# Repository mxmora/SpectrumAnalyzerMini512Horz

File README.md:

# SpectrumAnalyzerMini512Horz
SpectrumAnalyzerMini512Horz

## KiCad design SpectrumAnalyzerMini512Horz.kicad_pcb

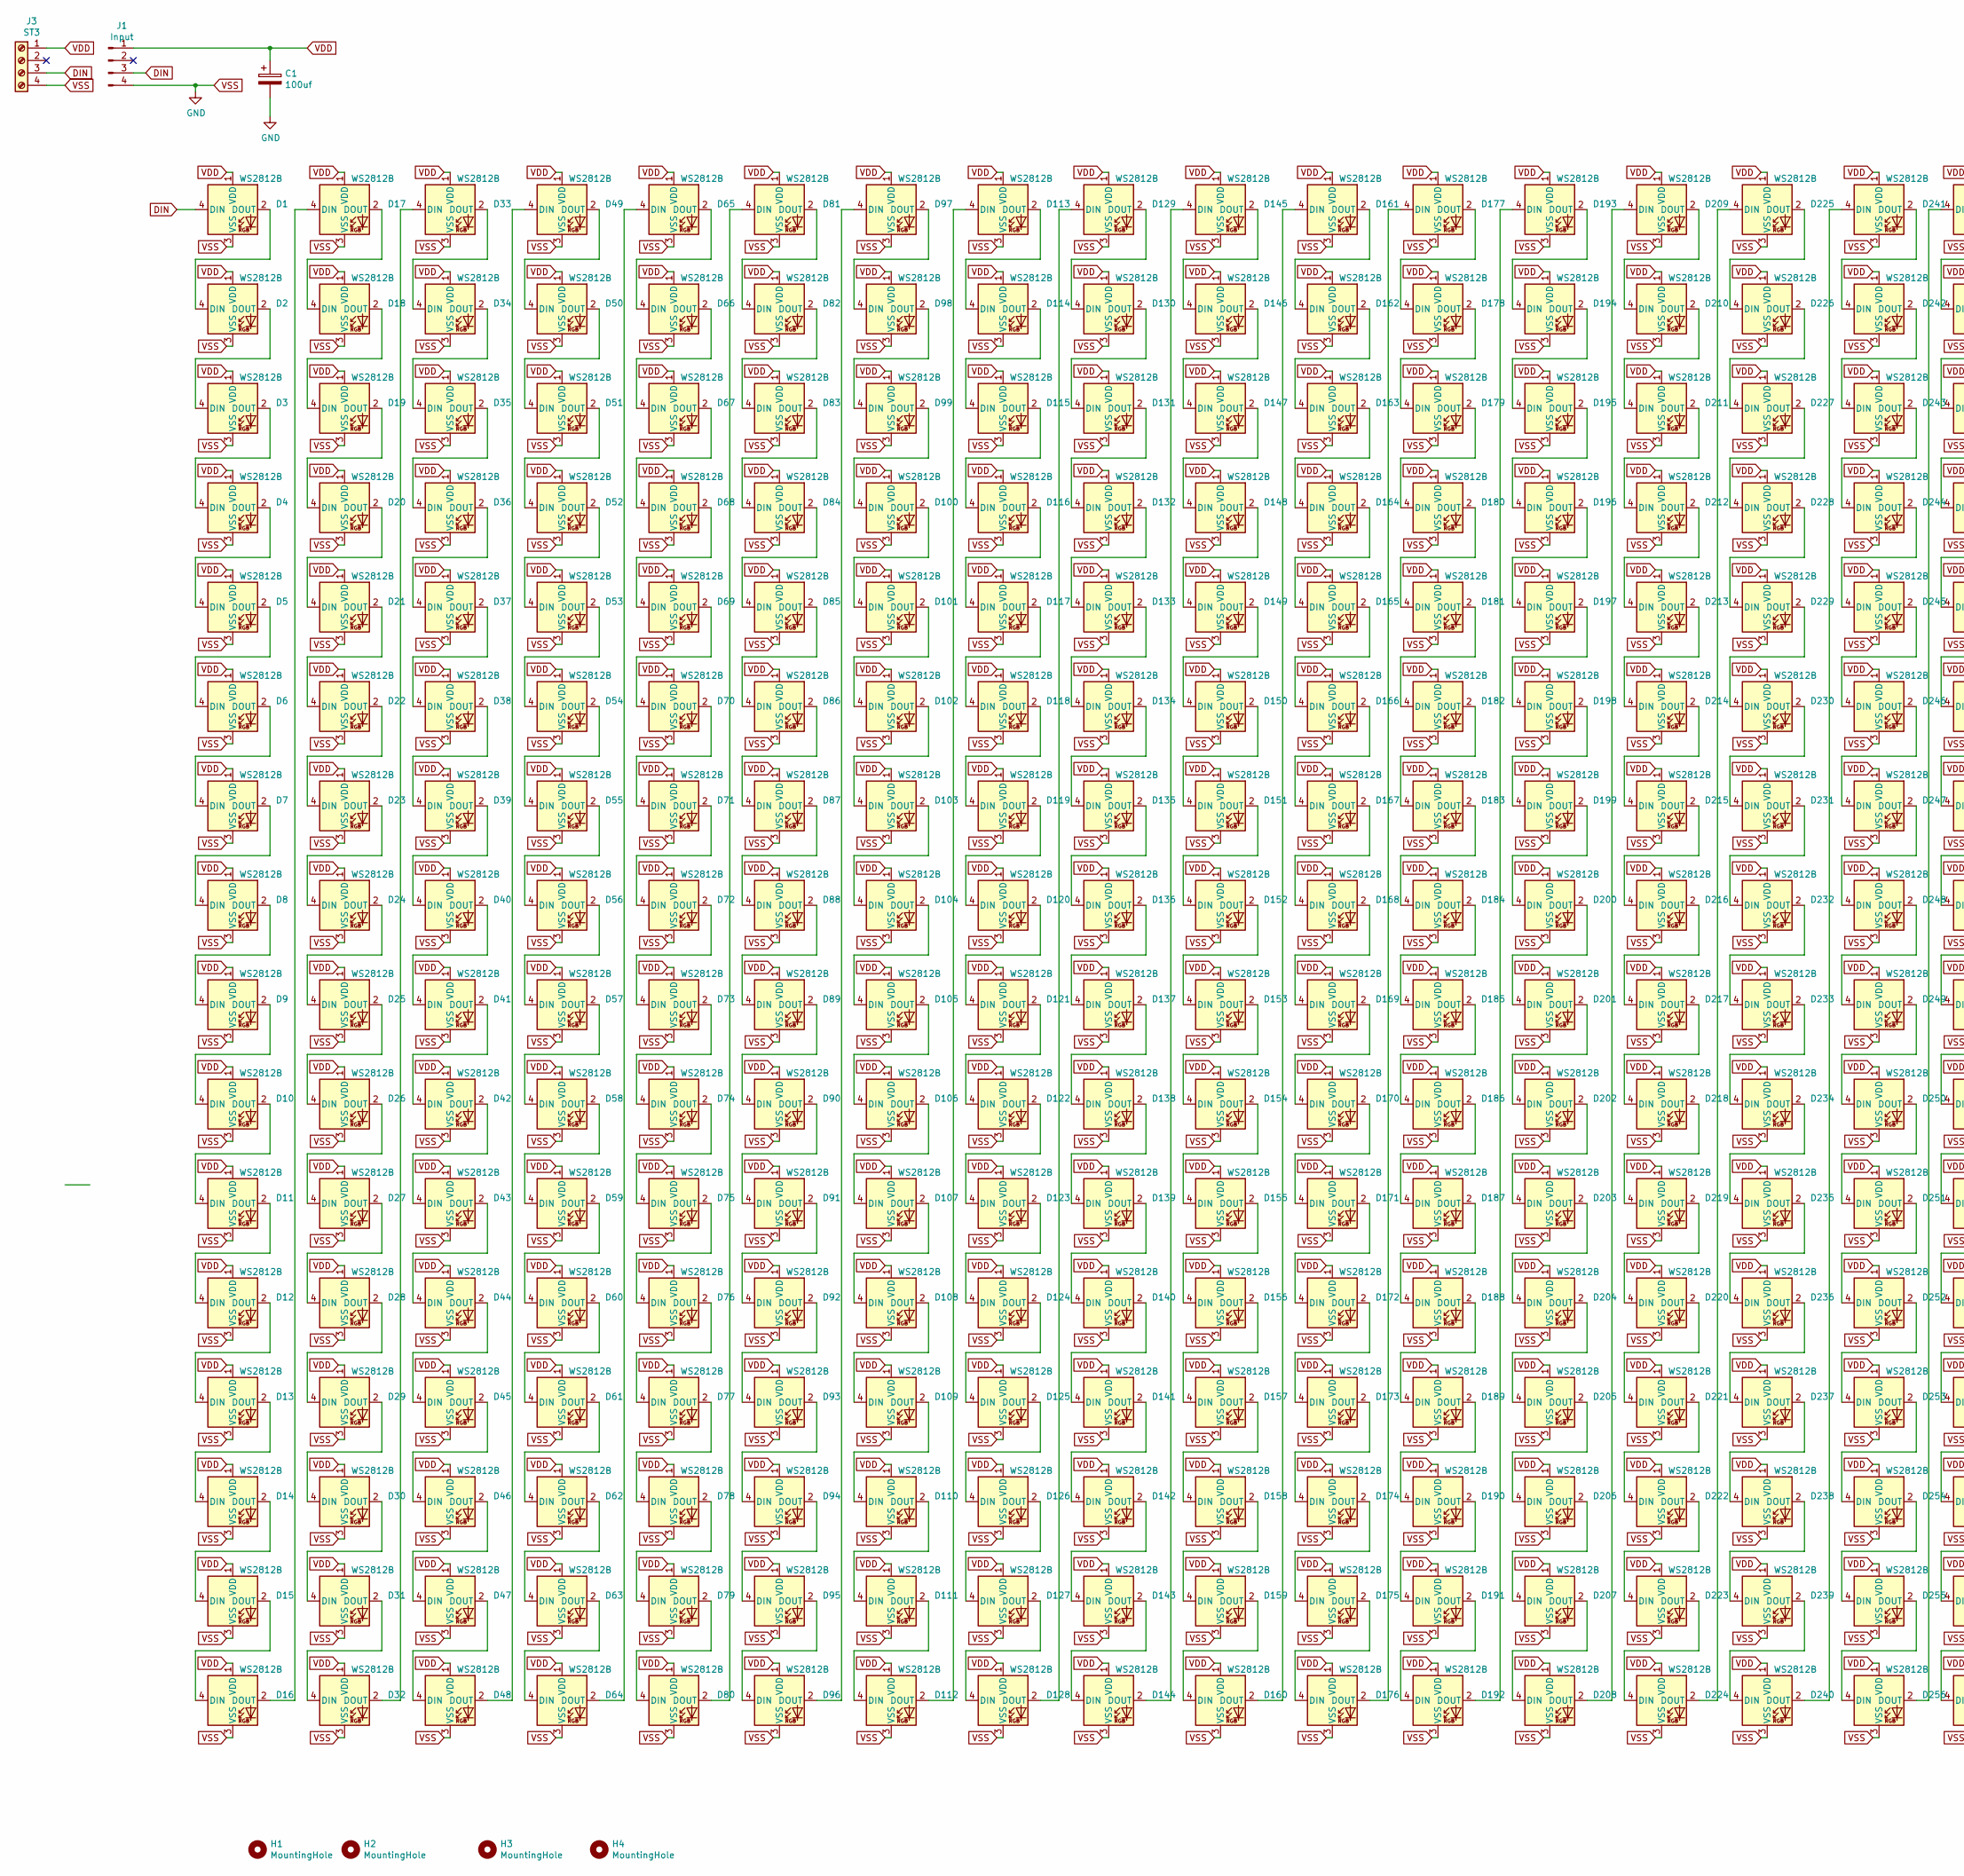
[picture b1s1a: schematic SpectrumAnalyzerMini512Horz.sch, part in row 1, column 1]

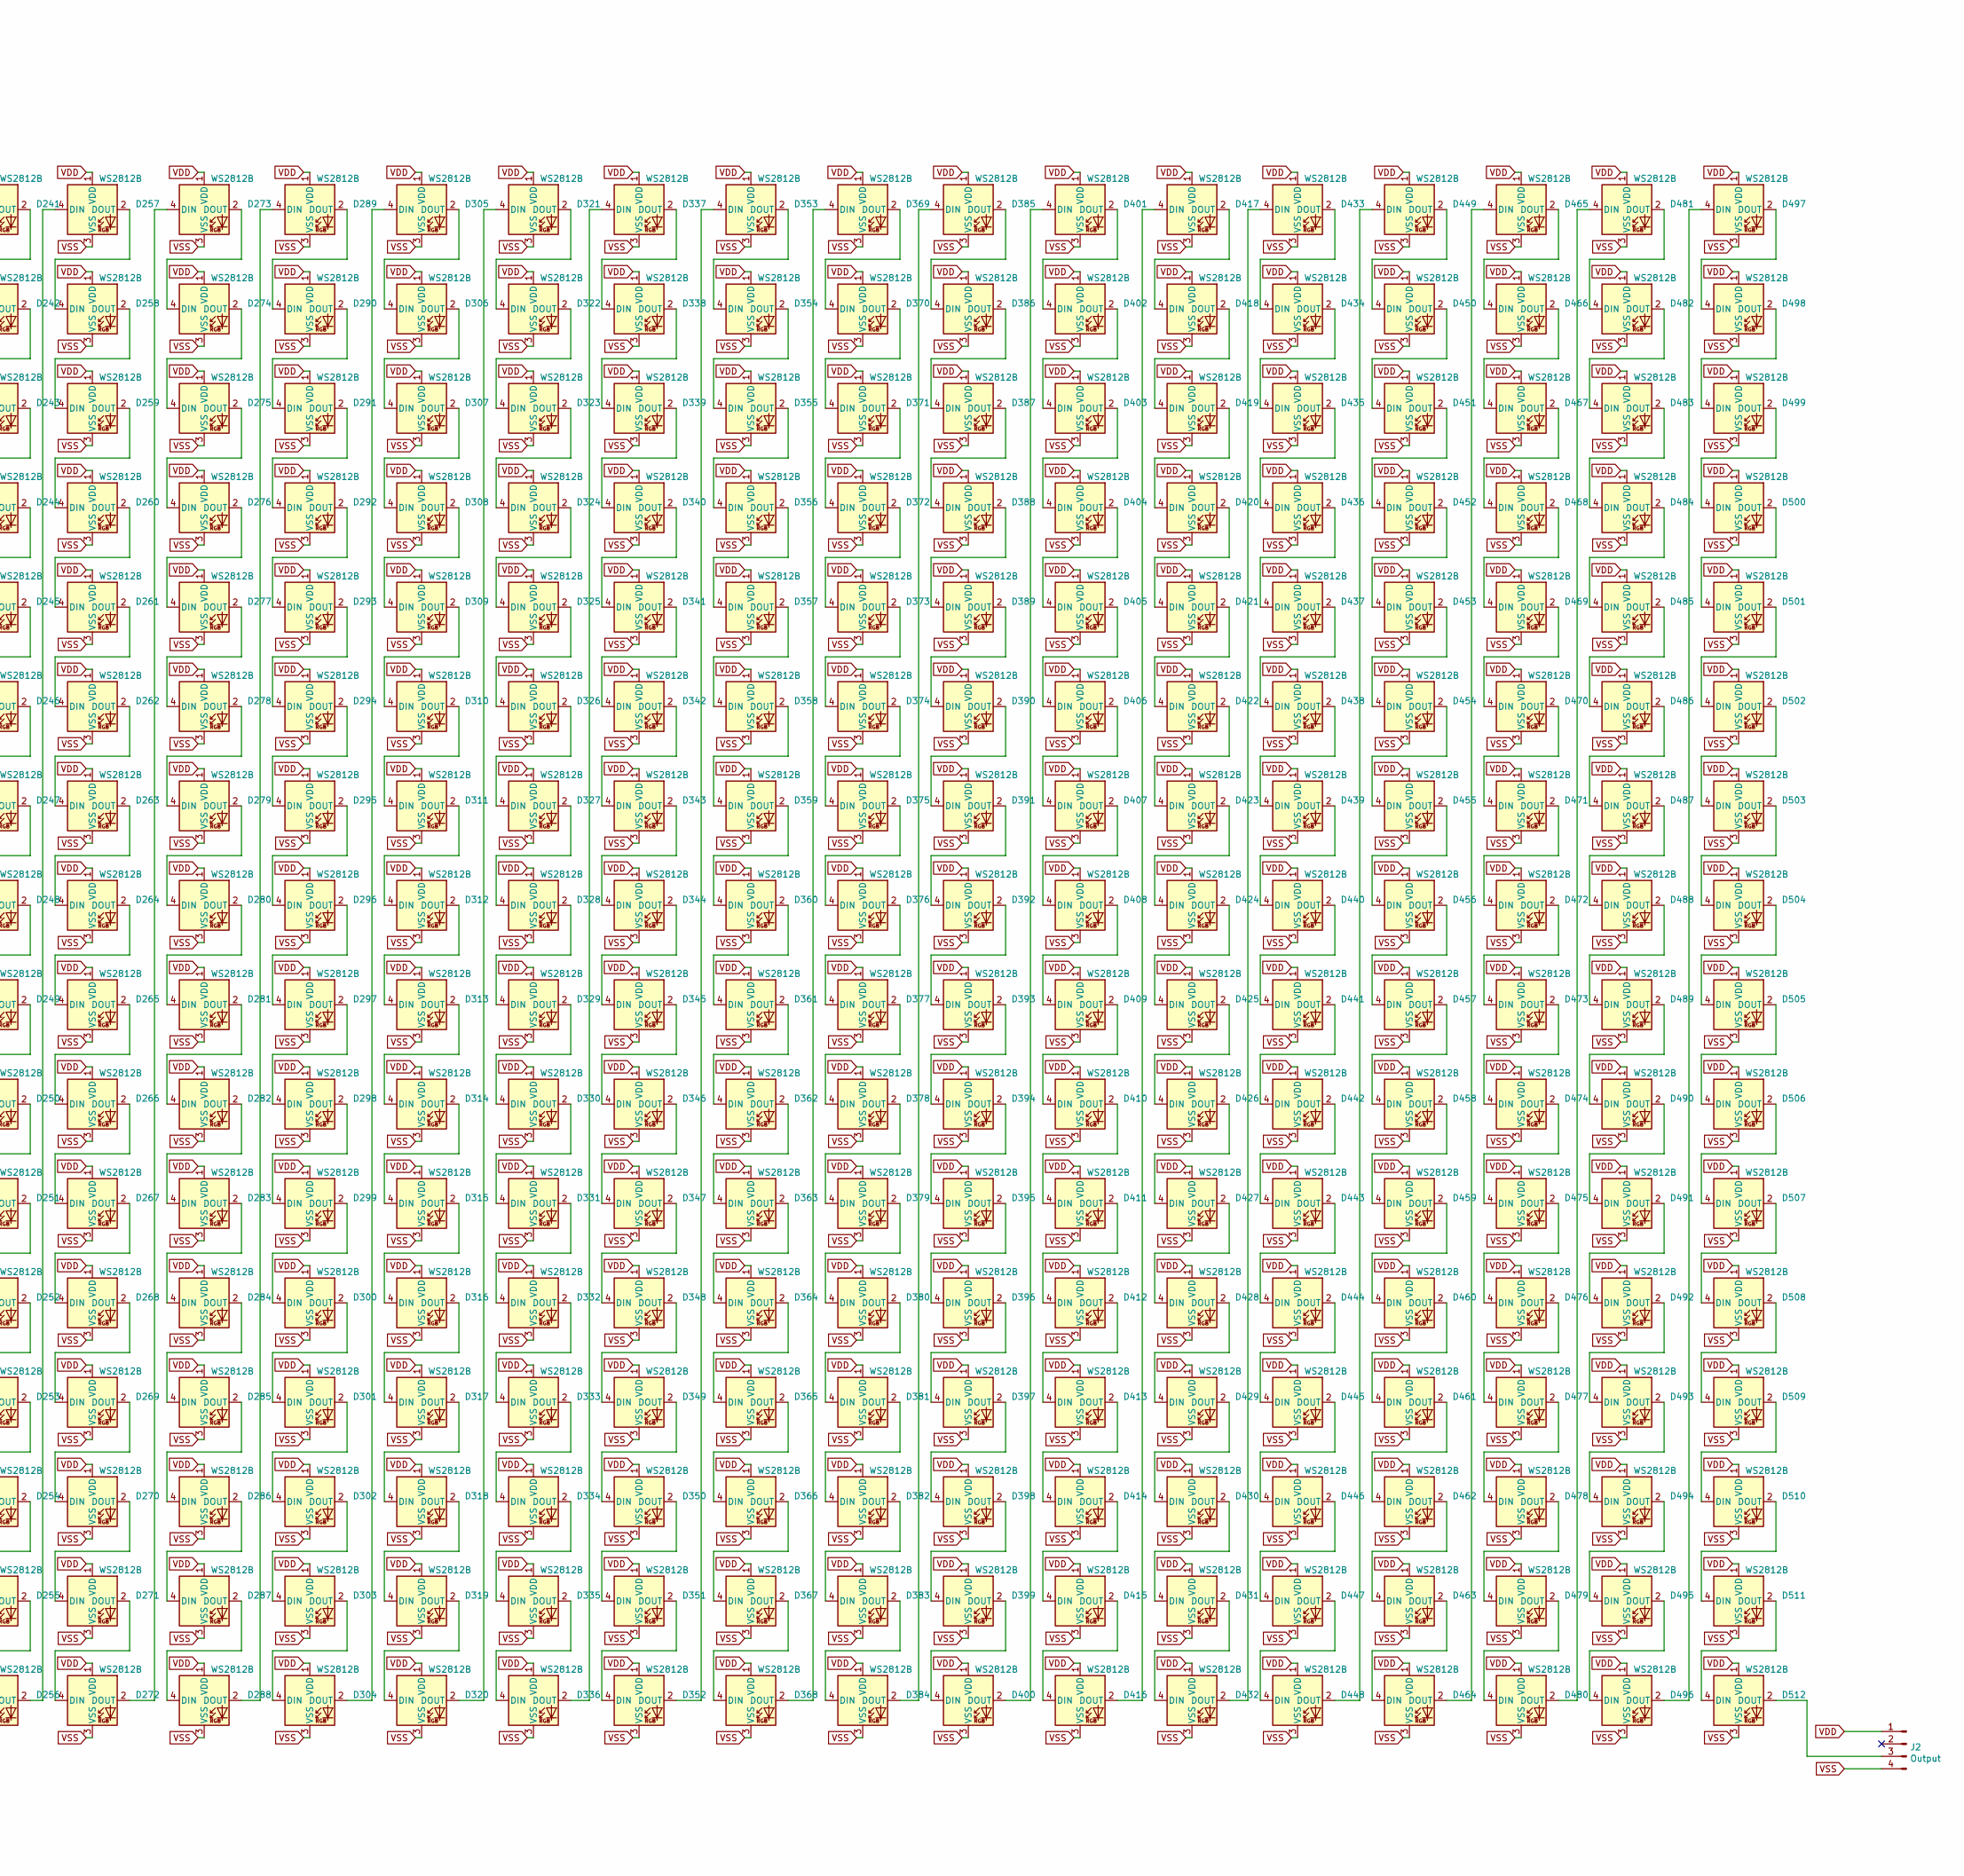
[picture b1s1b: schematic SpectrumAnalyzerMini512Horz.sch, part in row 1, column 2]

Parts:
C1: 100uf; CP_Radial_D5.0mm_P2.50mm
D1, D257: WS2812B; LED_SK6812MINI_PLCC4_3.5x3.5mm_P1.75mm; LCSC C114586
D2, D3, D4, D5, D6, D7, D8, D9, D10, D11, D12, D13, D14, D15, D16, D17, D18, D19, D20, D21, D22, D23, D24, D25, D26, D27, D28, D29, D30, D31, D32, D33, D34, D35, D36, D37, D38, D39, D40, D41, D42, D43, D44, D45, D46, D47, D48, D49, D50, D51, D52, D53, D54, D55, D56, D57, D58, D59, D60, D61, D62, D63, D64, D65, D66, D67, D68, D69, D70, D71, D72, D73, D74, D75, D76, D77, D78, D79, D80, D81, D82, D83, D84, D85, D86, D87, D88, D89, D90, D91, D92, D93, D94, D95, D96, D97, D98, D99, D100, D101, D102, D103, D104, D105, D106, D107, D108, D109, D110, D111, D112, D113, D114, D115, D116, D117, D118, D119, D120, D121, D122, D123, D124, D125, D126, D127, D128, D129, D130, D131, D132, D133, D134, D135, D136, D137, D138, D139, D140, D141, D142, D143, D144, D145, D146, D147, D148, D149, D150, D151, D152, D153, D154, D155, D156, D157, D158, D159, D160, D161, D162, D163, D164, D165, D166, D167, D168, D169, D170, D171, D172, D173, D174, D175, D176, D177, D178, D179, D180, D181, D182, D183, D184, D185, D186, D187, D188, D189, D190, D191, D192, D193, D194, D195, D196, D197, D198, D199, D200, D201, D202, D203, D204, D205, D206, D207, D208, D209, D210, D211, D212, D213, D214, D215, D216, D217, D218, D219, D220, D221, D222, D223, D224, D225, D226, D227, D228, D229, D230, D231, D232, D233, D234, D235, D236, D237, D238, D239, D240, D241, D242, D243, D244, D245, D246, D247, D248, D249, D250, D251, D252, D253, D254, D255, D256, D258, D259, D260, D261, D262, D263, D264, D265, D266, D267, D268, D269, D270, D271, D272, D273, D274, D275, D276, D277, D278, D279, D280, D281, D282, D283, D284, D285, D286, D287, D288, D289, D290, D291, D292, D293, D294, D295, D296, D297, D298, D299, D300, D301, D302, D303, D304, D305, D306, D307, D308, D309, D310, D311, D312, D313, D314, D315, D316, D317, D318, D319, D320, D321, D322, D323, D324, D325, D326, D327, D328, D329, D330, D331, D332, D333, D334, D335, D336, D337, D338, D339, D340, D341, D342, D343, D344, D345, D346, D347, D348, D349, D350, D351, D352, D353, D354, D355, D356, D357, D358, D359, D360, D361, D362, D363, D364, D365, D366, D367, D368, D369, D370, D371, D372, D373, D374, D375, D376, D377, D378, D379, D380, D381, D382, D383, D384, D385, D386, D387, D388, D389, D390, D391, D392, D393, D394, D395, D396, D397, D398, D399, D400, D401, D402, D403, D404, D405, D406, D407, D408, D409, D410, D411, D412, D413, D414, D415, D416, D417, D418, D419, D420, D421, D422, D423, D424, D425, D426, D427, D428, D429, D430, D431, D432, D433, D434, D435, D436, D437, D438, D439, D440, D441, D442, D443, D444, D445, D446, D447, D448, D449, D450, D451, D452, D453, D454, D455, D456, D457, D458, D459, D460, D461, D462, D463, D464, D465, D466, D467, D468, D469, D470, D471, D472, D473, D474, D475, D476, D477, D478, D479, D480, D481, D482, D483, D484, D485, D486, D487, D488, D489, D490, D491, D492, D493, D494, D495, D496, D497, D498, D499, D500, D501, D502, D503, D504, D505, D506, D507, D508, D509, D510, D511, D512: WS2812B; LED_SK6812MINI_PLCC4_3.5x3.5mm_P1.75mm
H1, H2, H3, H4: MountingHole; MountingHole_2.5mm
J1: Input; PinHeader_1x04_P2.54mm_Vertical
J2: Output; PinHeader_1x04_P2.54mm_Vertical
J3: ST3; TerminalBlock_Phoenix_MPT-0,5-4-2.54_1x04_P2.54mm_Horizontal

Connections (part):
DIN: D1.4 (DIN), J1.3, J3.3
unnamed: D1.2 (DOUT), D2.4 (DIN)
unnamed: D2.2 (DOUT), D3.4 (DIN)
unnamed: D3.2 (DOUT), D4.4 (DIN)
unnamed: D4.2 (DOUT), D5.4 (DIN)
unnamed: D5.2 (DOUT), D6.4 (DIN)
unnamed: D6.2 (DOUT), D7.4 (DIN)
unnamed: D7.2 (DOUT), D8.4 (DIN)
unnamed: D8.2 (DOUT), D9.4 (DIN)
unnamed: D10.2 (DOUT), D11.4 (DIN)
unnamed: D9.2 (DOUT), D10.4 (DIN)
unnamed: D11.2 (DOUT), D12.4 (DIN)
unnamed: D12.2 (DOUT), D13.4 (DIN)
unnamed: D13.2 (DOUT), D14.4 (DIN)
unnamed: D14.2 (DOUT), D15.4 (DIN)
unnamed: D15.2 (DOUT), D16.4 (DIN)
unnamed: D16.2 (DOUT), D17.4 (DIN)
unnamed: D17.2 (DOUT), D18.4 (DIN)
unnamed: D18.2 (DOUT), D19.4 (DIN)
unnamed: D19.2 (DOUT), D20.4 (DIN)
unnamed: D20.2 (DOUT), D21.4 (DIN)
unnamed: D21.2 (DOUT), D22.4 (DIN)
unnamed: D22.2 (DOUT), D23.4 (DIN)
unnamed: D23.2 (DOUT), D24.4 (DIN)
unnamed: D24.2 (DOUT), D25.4 (DIN)
unnamed: D25.2 (DOUT), D26.4 (DIN)
unnamed: D26.2 (DOUT), D27.4 (DIN)
unnamed: D27.2 (DOUT), D28.4 (DIN)
unnamed: D28.2 (DOUT), D29.4 (DIN)
unnamed: D29.2 (DOUT), D30.4 (DIN)
unnamed: D30.2 (DOUT), D31.4 (DIN)
unnamed: D31.2 (DOUT), D32.4 (DIN)
unnamed: D32.2 (DOUT), D33.4 (DIN)
unnamed: D33.2 (DOUT), D34.4 (DIN)
unnamed: D34.2 (DOUT), D35.4 (DIN)
unnamed: D35.2 (DOUT), D36.4 (DIN)
unnamed: D36.2 (DOUT), D37.4 (DIN)
unnamed: D37.2 (DOUT), D38.4 (DIN)
unnamed: D38.2 (DOUT), D39.4 (DIN)
unnamed: D39.2 (DOUT), D40.4 (DIN)
unnamed: D40.2 (DOUT), D41.4 (DIN)
unnamed: D41.2 (DOUT), D42.4 (DIN)
unnamed: D42.2 (DOUT), D43.4 (DIN)
unnamed: D43.2 (DOUT), D44.4 (DIN)
unnamed: D44.2 (DOUT), D45.4 (DIN)
unnamed: D45.2 (DOUT), D46.4 (DIN)
unnamed: D46.2 (DOUT), D47.4 (DIN)
unnamed: D47.2 (DOUT), D48.4 (DIN)
unnamed: D48.2 (DOUT), D49.4 (DIN)
unnamed: D49.2 (DOUT), D50.4 (DIN)
unnamed: D50.2 (DOUT), D51.4 (DIN)
unnamed: D51.2 (DOUT), D52.4 (DIN)
unnamed: D52.2 (DOUT), D53.4 (DIN)
unnamed: D53.2 (DOUT), D54.4 (DIN)
unnamed: D54.2 (DOUT), D55.4 (DIN)
unnamed: D55.2 (DOUT), D56.4 (DIN)
unnamed: D56.2 (DOUT), D57.4 (DIN)
unnamed: D57.2 (DOUT), D58.4 (DIN)
unnamed: D58.2 (DOUT), D59.4 (DIN)
unnamed: D59.2 (DOUT), D60.4 (DIN)
unnamed: D60.2 (DOUT), D61.4 (DIN)
unnamed: D61.2 (DOUT), D62.4 (DIN)
unnamed: D62.2 (DOUT), D63.4 (DIN)
unnamed: D63.2 (DOUT), D64.4 (DIN)
unnamed: D64.2 (DOUT), D65.4 (DIN)
unnamed: D65.2 (DOUT), D66.4 (DIN)
unnamed: D66.2 (DOUT), D67.4 (DIN)
unnamed: D67.2 (DOUT), D68.4 (DIN)
unnamed: D68.2 (DOUT), D69.4 (DIN)
unnamed: D69.2 (DOUT), D70.4 (DIN)
unnamed: D70.2 (DOUT), D71.4 (DIN)
unnamed: D71.2 (DOUT), D72.4 (DIN)
unnamed: D72.2 (DOUT), D73.4 (DIN)
unnamed: D73.2 (DOUT), D74.4 (DIN)
unnamed: D74.2 (DOUT), D75.4 (DIN)
unnamed: D75.2 (DOUT), D76.4 (DIN)
unnamed: D76.2 (DOUT), D77.4 (DIN)
unnamed: D77.2 (DOUT), D78.4 (DIN)
unnamed: D78.2 (DOUT), D79.4 (DIN)
unnamed: D79.2 (DOUT), D80.4 (DIN)
unnamed: D80.2 (DOUT), D81.4 (DIN)
unnamed: D81.2 (DOUT), D82.4 (DIN)
unnamed: D82.2 (DOUT), D83.4 (DIN)
unnamed: D83.2 (DOUT), D84.4 (DIN)
unnamed: D84.2 (DOUT), D85.4 (DIN)
unnamed: D85.2 (DOUT), D86.4 (DIN)
unnamed: D86.2 (DOUT), D87.4 (DIN)
unnamed: D87.2 (DOUT), D88.4 (DIN)
unnamed: D88.2 (DOUT), D89.4 (DIN)
unnamed: D89.2 (DOUT), D90.4 (DIN)
unnamed: D90.2 (DOUT), D91.4 (DIN)
unnamed: D91.2 (DOUT), D92.4 (DIN)
unnamed: D92.2 (DOUT), D93.4 (DIN)
unnamed: D93.2 (DOUT), D94.4 (DIN)
unnamed: D94.2 (DOUT), D95.4 (DIN)
unnamed: D95.2 (DOUT), D96.4 (DIN)
unnamed: D96.2 (DOUT), D97.4 (DIN)
unnamed: D97.2 (DOUT), D98.4 (DIN)
unnamed: D98.2 (DOUT), D99.4 (DIN)
unnamed: D100.2 (DOUT), D101.4 (DIN)
unnamed: D99.2 (DOUT), D100.4 (DIN)
unnamed: D101.2 (DOUT), D102.4 (DIN)
unnamed: D102.2 (DOUT), D103.4 (DIN)
unnamed: D103.2 (DOUT), D104.4 (DIN)
unnamed: D104.2 (DOUT), D105.4 (DIN)
unnamed: D105.2 (DOUT), D106.4 (DIN)
unnamed: D106.2 (DOUT), D107.4 (DIN)
unnamed: D107.2 (DOUT), D108.4 (DIN)
unnamed: D108.2 (DOUT), D109.4 (DIN)
unnamed: D109.2 (DOUT), D110.4 (DIN)
unnamed: D110.2 (DOUT), D111.4 (DIN)
unnamed: D111.2 (DOUT), D112.4 (DIN)
unnamed: D112.2 (DOUT), D113.4 (DIN)
unnamed: D113.2 (DOUT), D114.4 (DIN)
unnamed: D114.2 (DOUT), D115.4 (DIN)
unnamed: D115.2 (DOUT), D116.4 (DIN)
unnamed: D116.2 (DOUT), D117.4 (DIN)
unnamed: D117.2 (DOUT), D118.4 (DIN)
unnamed: D118.2 (DOUT), D119.4 (DIN)
unnamed: D119.2 (DOUT), D120.4 (DIN)
unnamed: D120.2 (DOUT), D121.4 (DIN)
unnamed: D121.2 (DOUT), D122.4 (DIN)
unnamed: D122.2 (DOUT), D123.4 (DIN)
unnamed: D123.2 (DOUT), D124.4 (DIN)
unnamed: D124.2 (DOUT), D125.4 (DIN)
unnamed: D125.2 (DOUT), D126.4 (DIN)
unnamed: D126.2 (DOUT), D127.4 (DIN)
unnamed: D127.2 (DOUT), D128.4 (DIN)
unnamed: D128.2 (DOUT), D129.4 (DIN)
unnamed: D129.2 (DOUT), D130.4 (DIN)
unnamed: D130.2 (DOUT), D131.4 (DIN)
unnamed: D131.2 (DOUT), D132.4 (DIN)
unnamed: D132.2 (DOUT), D133.4 (DIN)
unnamed: D133.2 (DOUT), D134.4 (DIN)
unnamed: D134.2 (DOUT), D135.4 (DIN)
unnamed: D135.2 (DOUT), D136.4 (DIN)
unnamed: D136.2 (DOUT), D137.4 (DIN)
unnamed: D137.2 (DOUT), D138.4 (DIN)
unnamed: D138.2 (DOUT), D139.4 (DIN)
unnamed: D139.2 (DOUT), D140.4 (DIN)
unnamed: D140.2 (DOUT), D141.4 (DIN)
unnamed: D141.2 (DOUT), D142.4 (DIN)
unnamed: D142.2 (DOUT), D143.4 (DIN)
unnamed: D143.2 (DOUT), D144.4 (DIN)
unnamed: D144.2 (DOUT), D145.4 (DIN)
unnamed: D145.2 (DOUT), D146.4 (DIN)
unnamed: D146.2 (DOUT), D147.4 (DIN)
unnamed: D147.2 (DOUT), D148.4 (DIN)
unnamed: D148.2 (DOUT), D149.4 (DIN)
unnamed: D149.2 (DOUT), D150.4 (DIN)
unnamed: D150.2 (DOUT), D151.4 (DIN)
unnamed: D151.2 (DOUT), D152.4 (DIN)
unnamed: D152.2 (DOUT), D153.4 (DIN)
unnamed: D153.2 (DOUT), D154.4 (DIN)
unnamed: D154.2 (DOUT), D155.4 (DIN)
unnamed: D155.2 (DOUT), D156.4 (DIN)
unnamed: D156.2 (DOUT), D157.4 (DIN)
unnamed: D157.2 (DOUT), D158.4 (DIN)
unnamed: D158.2 (DOUT), D159.4 (DIN)
unnamed: D159.2 (DOUT), D160.4 (DIN)
unnamed: D160.2 (DOUT), D161.4 (DIN)
unnamed: D161.2 (DOUT), D162.4 (DIN)
unnamed: D162.2 (DOUT), D163.4 (DIN)
unnamed: D163.2 (DOUT), D164.4 (DIN)
unnamed: D164.2 (DOUT), D165.4 (DIN)
unnamed: D165.2 (DOUT), D166.4 (DIN)
unnamed: D166.2 (DOUT), D167.4 (DIN)
unnamed: D167.2 (DOUT), D168.4 (DIN)
unnamed: D168.2 (DOUT), D169.4 (DIN)
unnamed: D169.2 (DOUT), D170.4 (DIN)
unnamed: D170.2 (DOUT), D171.4 (DIN)
unnamed: D171.2 (DOUT), D172.4 (DIN)
unnamed: D172.2 (DOUT), D173.4 (DIN)
unnamed: D173.2 (DOUT), D174.4 (DIN)
unnamed: D174.2 (DOUT), D175.4 (DIN)
unnamed: D175.2 (DOUT), D176.4 (DIN)
unnamed: D176.2 (DOUT), D177.4 (DIN)
unnamed: D177.2 (DOUT), D178.4 (DIN)
unnamed: D178.2 (DOUT), D179.4 (DIN)
unnamed: D179.2 (DOUT), D180.4 (DIN)
unnamed: D180.2 (DOUT), D181.4 (DIN)
unnamed: D181.2 (DOUT), D182.4 (DIN)
unnamed: D182.2 (DOUT), D183.4 (DIN)
unnamed: D183.2 (DOUT), D184.4 (DIN)
unnamed: D184.2 (DOUT), D185.4 (DIN)
unnamed: D185.2 (DOUT), D186.4 (DIN)
unnamed: D186.2 (DOUT), D187.4 (DIN)
unnamed: D187.2 (DOUT), D188.4 (DIN)
unnamed: D188.2 (DOUT), D189.4 (DIN)
unnamed: D189.2 (DOUT), D190.4 (DIN)
unnamed: D190.2 (DOUT), D191.4 (DIN)
unnamed: D191.2 (DOUT), D192.4 (DIN)
unnamed: D192.2 (DOUT), D193.4 (DIN)
unnamed: D193.2 (DOUT), D194.4 (DIN)
unnamed: D194.2 (DOUT), D195.4 (DIN)
unnamed: D195.2 (DOUT), D196.4 (DIN)
unnamed: D196.2 (DOUT), D197.4 (DIN)
unnamed: D197.2 (DOUT), D198.4 (DIN)
unnamed: D198.2 (DOUT), D199.4 (DIN)
unnamed: D199.2 (DOUT), D200.4 (DIN)
unnamed: D200.2 (DOUT), D201.4 (DIN)
unnamed: D201.2 (DOUT), D202.4 (DIN)
unnamed: D202.2 (DOUT), D203.4 (DIN)
unnamed: D203.2 (DOUT), D204.4 (DIN)
unnamed: D204.2 (DOUT), D205.4 (DIN)
unnamed: D205.2 (DOUT), D206.4 (DIN)
unnamed: D206.2 (DOUT), D207.4 (DIN)
unnamed: D207.2 (DOUT), D208.4 (DIN)
unnamed: D208.2 (DOUT), D209.4 (DIN)
unnamed: D209.2 (DOUT), D210.4 (DIN)
unnamed: D210.2 (DOUT), D211.4 (DIN)
unnamed: D211.2 (DOUT), D212.4 (DIN)
unnamed: D212.2 (DOUT), D213.4 (DIN)
unnamed: D213.2 (DOUT), D214.4 (DIN)
unnamed: D214.2 (DOUT), D215.4 (DIN)
unnamed: D215.2 (DOUT), D216.4 (DIN)
unnamed: D216.2 (DOUT), D217.4 (DIN)
unnamed: D217.2 (DOUT), D218.4 (DIN)
unnamed: D218.2 (DOUT), D219.4 (DIN)
unnamed: D219.2 (DOUT), D220.4 (DIN)
unnamed: D220.2 (DOUT), D221.4 (DIN)
unnamed: D221.2 (DOUT), D222.4 (DIN)
unnamed: D222.2 (DOUT), D223.4 (DIN)
unnamed: D223.2 (DOUT), D224.4 (DIN)
unnamed: D224.2 (DOUT), D225.4 (DIN)
unnamed: D225.2 (DOUT), D226.4 (DIN)
unnamed: D226.2 (DOUT), D227.4 (DIN)
unnamed: D227.2 (DOUT), D228.4 (DIN)
unnamed: D228.2 (DOUT), D229.4 (DIN)
unnamed: D229.2 (DOUT), D230.4 (DIN)
unnamed: D230.2 (DOUT), D231.4 (DIN)
unnamed: D231.2 (DOUT), D232.4 (DIN)
unnamed: D232.2 (DOUT), D233.4 (DIN)
unnamed: D233.2 (DOUT), D234.4 (DIN)
unnamed: D234.2 (DOUT), D235.4 (DIN)
unnamed: D235.2 (DOUT), D236.4 (DIN)
unnamed: D236.2 (DOUT), D237.4 (DIN)
unnamed: D237.2 (DOUT), D238.4 (DIN)
unnamed: D238.2 (DOUT), D239.4 (DIN)
unnamed: D239.2 (DOUT), D240.4 (DIN)
unnamed: D240.2 (DOUT), D241.4 (DIN)
unnamed: D241.2 (DOUT), D242.4 (DIN)
unnamed: D242.2 (DOUT), D243.4 (DIN)
unnamed: D243.2 (DOUT), D244.4 (DIN)
unnamed: D244.2 (DOUT), D245.4 (DIN)
unnamed: D245.2 (DOUT), D246.4 (DIN)
unnamed: D246.2 (DOUT), D247.4 (DIN)
unnamed: D247.2 (DOUT), D248.4 (DIN)
unnamed: D248.2 (DOUT), D249.4 (DIN)
unnamed: D249.2 (DOUT), D250.4 (DIN)
unnamed: D250.2 (DOUT), D251.4 (DIN)
unnamed: D251.2 (DOUT), D252.4 (DIN)
unnamed: D252.2 (DOUT), D253.4 (DIN)
unnamed: D253.2 (DOUT), D254.4 (DIN)
unnamed: D254.2 (DOUT), D255.4 (DIN)
unnamed: D255.2 (DOUT), D256.4 (DIN)
unnamed: D256.2 (DOUT), D257.4 (DIN)
unnamed: D257.2 (DOUT), D258.4 (DIN)
unnamed: D258.2 (DOUT), D259.4 (DIN)
unnamed: D259.2 (DOUT), D260.4 (DIN)
unnamed: D260.2 (DOUT), D261.4 (DIN)
unnamed: D261.2 (DOUT), D262.4 (DIN)
unnamed: D262.2 (DOUT), D263.4 (DIN)
unnamed: D263.2 (DOUT), D264.4 (DIN)
unnamed: D264.2 (DOUT), D265.4 (DIN)
unnamed: D265.2 (DOUT), D266.4 (DIN)
unnamed: D266.2 (DOUT), D267.4 (DIN)
unnamed: D267.2 (DOUT), D268.4 (DIN)
unnamed: D268.2 (DOUT), D269.4 (DIN)
unnamed: D269.2 (DOUT), D270.4 (DIN)
unnamed: D270.2 (DOUT), D271.4 (DIN)
unnamed: D271.2 (DOUT), D272.4 (DIN)
unnamed: D272.2 (DOUT), D273.4 (DIN)
unnamed: D273.2 (DOUT), D274.4 (DIN)
unnamed: D274.2 (DOUT), D275.4 (DIN)
unnamed: D275.2 (DOUT), D276.4 (DIN)
unnamed: D276.2 (DOUT), D277.4 (DIN)
unnamed: D277.2 (DOUT), D278.4 (DIN)
unnamed: D278.2 (DOUT), D279.4 (DIN)
unnamed: D279.2 (DOUT), D280.4 (DIN)
unnamed: D280.2 (DOUT), D281.4 (DIN)
unnamed: D281.2 (DOUT), D282.4 (DIN)
unnamed: D282.2 (DOUT), D283.4 (DIN)
unnamed: D283.2 (DOUT), D284.4 (DIN)
unnamed: D284.2 (DOUT), D285.4 (DIN)
unnamed: D285.2 (DOUT), D286.4 (DIN)
unnamed: D286.2 (DOUT), D287.4 (DIN)
unnamed: D287.2 (DOUT), D288.4 (DIN)
unnamed: D288.2 (DOUT), D289.4 (DIN)
unnamed: D289.2 (DOUT), D290.4 (DIN)
unnamed: D290.2 (DOUT), D291.4 (DIN)
unnamed: D291.2 (DOUT), D292.4 (DIN)
unnamed: D292.2 (DOUT), D293.4 (DIN)
unnamed: D293.2 (DOUT), D294.4 (DIN)
unnamed: D294.2 (DOUT), D295.4 (DIN)
unnamed: D295.2 (DOUT), D296.4 (DIN)
unnamed: D296.2 (DOUT), D297.4 (DIN)
unnamed: D297.2 (DOUT), D298.4 (DIN)
unnamed: D298.2 (DOUT), D299.4 (DIN)
unnamed: D299.2 (DOUT), D300.4 (DIN)
unnamed: D300.2 (DOUT), D301.4 (DIN)
unnamed: D301.2 (DOUT), D302.4 (DIN)
unnamed: D302.2 (DOUT), D303.4 (DIN)
unnamed: D303.2 (DOUT), D304.4 (DIN)
unnamed: D304.2 (DOUT), D305.4 (DIN)
unnamed: D305.2 (DOUT), D306.4 (DIN)
unnamed: D306.2 (DOUT), D307.4 (DIN)
unnamed: D307.2 (DOUT), D308.4 (DIN)
unnamed: D308.2 (DOUT), D309.4 (DIN)
unnamed: D309.2 (DOUT), D310.4 (DIN)
unnamed: D310.2 (DOUT), D311.4 (DIN)
unnamed: D311.2 (DOUT), D312.4 (DIN)
unnamed: D312.2 (DOUT), D313.4 (DIN)
unnamed: D313.2 (DOUT), D314.4 (DIN)
unnamed: D314.2 (DOUT), D315.4 (DIN)
unnamed: D315.2 (DOUT), D316.4 (DIN)
unnamed: D316.2 (DOUT), D317.4 (DIN)
unnamed: D317.2 (DOUT), D318.4 (DIN)
unnamed: D318.2 (DOUT), D319.4 (DIN)
unnamed: D319.2 (DOUT), D320.4 (DIN)
unnamed: D320.2 (DOUT), D321.4 (DIN)
unnamed: D321.2 (DOUT), D322.4 (DIN)
unnamed: D322.2 (DOUT), D323.4 (DIN)
unnamed: D323.2 (DOUT), D324.4 (DIN)
unnamed: D324.2 (DOUT), D325.4 (DIN)
unnamed: D325.2 (DOUT), D326.4 (DIN)
unnamed: D326.2 (DOUT), D327.4 (DIN)
unnamed: D327.2 (DOUT), D328.4 (DIN)
unnamed: D328.2 (DOUT), D329.4 (DIN)
unnamed: D329.2 (DOUT), D330.4 (DIN)
unnamed: D330.2 (DOUT), D331.4 (DIN)
unnamed: D331.2 (DOUT), D332.4 (DIN)
unnamed: D332.2 (DOUT), D333.4 (DIN)
unnamed: D333.2 (DOUT), D334.4 (DIN)
unnamed: D334.2 (DOUT), D335.4 (DIN)
unnamed: D335.2 (DOUT), D336.4 (DIN)
unnamed: D336.2 (DOUT), D337.4 (DIN)
unnamed: D337.2 (DOUT), D338.4 (DIN)
unnamed: D338.2 (DOUT), D339.4 (DIN)
unnamed: D339.2 (DOUT), D340.4 (DIN)
unnamed: D340.2 (DOUT), D341.4 (DIN)
unnamed: D341.2 (DOUT), D342.4 (DIN)
unnamed: D342.2 (DOUT), D343.4 (DIN)
unnamed: D343.2 (DOUT), D344.4 (DIN)
unnamed: D344.2 (DOUT), D345.4 (DIN)
unnamed: D345.2 (DOUT), D346.4 (DIN)
unnamed: D346.2 (DOUT), D347.4 (DIN)
unnamed: D347.2 (DOUT), D348.4 (DIN)
unnamed: D348.2 (DOUT), D349.4 (DIN)
unnamed: D349.2 (DOUT), D350.4 (DIN)
unnamed: D350.2 (DOUT), D351.4 (DIN)
unnamed: D351.2 (DOUT), D352.4 (DIN)
unnamed: D352.2 (DOUT), D353.4 (DIN)
unnamed: D353.2 (DOUT), D354.4 (DIN)
unnamed: D354.2 (DOUT), D355.4 (DIN)
unnamed: D355.2 (DOUT), D356.4 (DIN)
unnamed: D356.2 (DOUT), D357.4 (DIN)
unnamed: D357.2 (DOUT), D358.4 (DIN)
unnamed: D358.2 (DOUT), D359.4 (DIN)
unnamed: D359.2 (DOUT), D360.4 (DIN)
unnamed: D360.2 (DOUT), D361.4 (DIN)
unnamed: D361.2 (DOUT), D362.4 (DIN)
unnamed: D362.2 (DOUT), D363.4 (DIN)
unnamed: D363.2 (DOUT), D364.4 (DIN)
unnamed: D364.2 (DOUT), D365.4 (DIN)
unnamed: D365.2 (DOUT), D366.4 (DIN)
unnamed: D366.2 (DOUT), D367.4 (DIN)
unnamed: D367.2 (DOUT), D368.4 (DIN)
unnamed: D368.2 (DOUT), D369.4 (DIN)
unnamed: D369.2 (DOUT), D370.4 (DIN)
unnamed: D370.2 (DOUT), D371.4 (DIN)
unnamed: D371.2 (DOUT), D372.4 (DIN)
unnamed: D372.2 (DOUT), D373.4 (DIN)
unnamed: D373.2 (DOUT), D374.4 (DIN)
unnamed: D374.2 (DOUT), D375.4 (DIN)
unnamed: D375.2 (DOUT), D376.4 (DIN)
unnamed: D376.2 (DOUT), D377.4 (DIN)
unnamed: D377.2 (DOUT), D378.4 (DIN)
unnamed: D378.2 (DOUT), D379.4 (DIN)
unnamed: D379.2 (DOUT), D380.4 (DIN)
unnamed: D380.2 (DOUT), D381.4 (DIN)
unnamed: D381.2 (DOUT), D382.4 (DIN)
unnamed: D382.2 (DOUT), D383.4 (DIN)
unnamed: D383.2 (DOUT), D384.4 (DIN)
unnamed: D384.2 (DOUT), D385.4 (DIN)
unnamed: D385.2 (DOUT), D386.4 (DIN)
unnamed: D386.2 (DOUT), D387.4 (DIN)
unnamed: D387.2 (DOUT), D388.4 (DIN)
unnamed: D388.2 (DOUT), D389.4 (DIN)
unnamed: D389.2 (DOUT), D390.4 (DIN)
unnamed: D390.2 (DOUT), D391.4 (DIN)
unnamed: D391.2 (DOUT), D392.4 (DIN)
unnamed: D392.2 (DOUT), D393.4 (DIN)
unnamed: D393.2 (DOUT), D394.4 (DIN)
unnamed: D394.2 (DOUT), D395.4 (DIN)
unnamed: D395.2 (DOUT), D396.4 (DIN)
unnamed: D396.2 (DOUT), D397.4 (DIN)
unnamed: D397.2 (DOUT), D398.4 (DIN)
unnamed: D398.2 (DOUT), D399.4 (DIN)
unnamed: D399.2 (DOUT), D400.4 (DIN)
unnamed: D400.2 (DOUT), D401.4 (DIN)
unnamed: D401.2 (DOUT), D402.4 (DIN)
unnamed: D402.2 (DOUT), D403.4 (DIN)
unnamed: D403.2 (DOUT), D404.4 (DIN)
unnamed: D404.2 (DOUT), D405.4 (DIN)
unnamed: D405.2 (DOUT), D406.4 (DIN)
unnamed: D406.2 (DOUT), D407.4 (DIN)
unnamed: D407.2 (DOUT), D408.4 (DIN)
unnamed: D408.2 (DOUT), D409.4 (DIN)
unnamed: D409.2 (DOUT), D410.4 (DIN)
unnamed: D410.2 (DOUT), D411.4 (DIN)
unnamed: D411.2 (DOUT), D412.4 (DIN)
unnamed: D412.2 (DOUT), D413.4 (DIN)
unnamed: D413.2 (DOUT), D414.4 (DIN)
unnamed: D414.2 (DOUT), D415.4 (DIN)
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
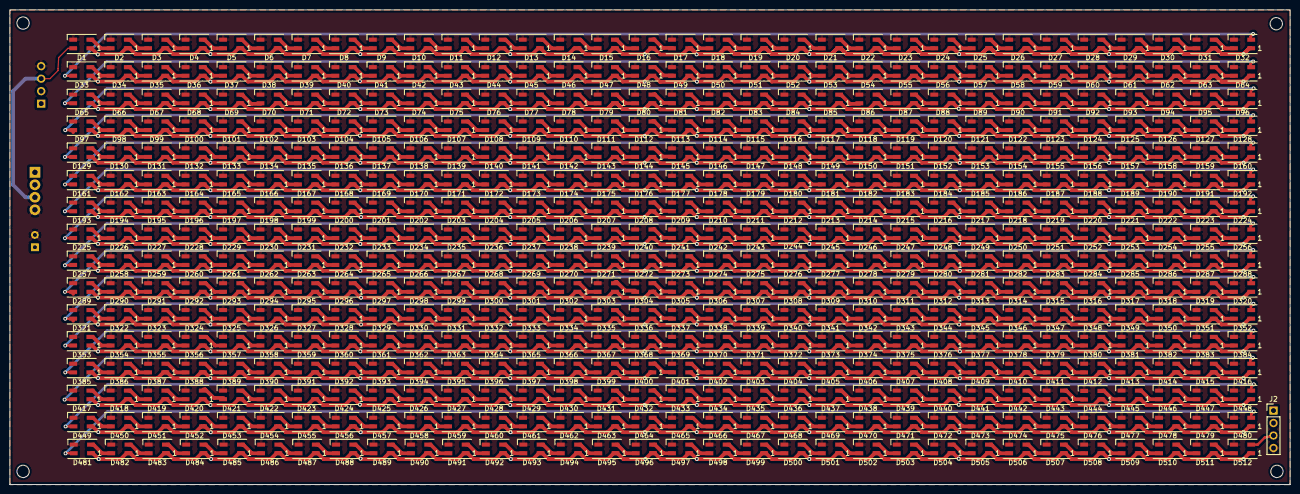
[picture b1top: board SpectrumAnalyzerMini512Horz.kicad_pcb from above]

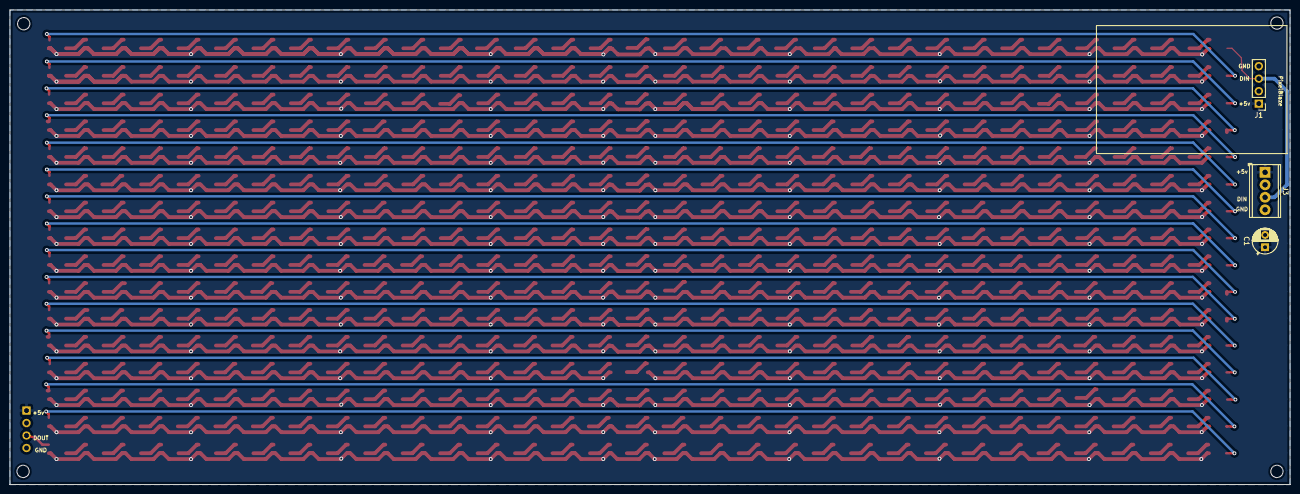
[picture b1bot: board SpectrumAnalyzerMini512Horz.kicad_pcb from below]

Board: 2 copper layers, 260.4 x 96.5 mm, 520 parts (3 on the bottom side), 515 nets.

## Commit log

2020-11-21 first check in
2020-11-21 remove finder file
2020-11-21 update gitignore
